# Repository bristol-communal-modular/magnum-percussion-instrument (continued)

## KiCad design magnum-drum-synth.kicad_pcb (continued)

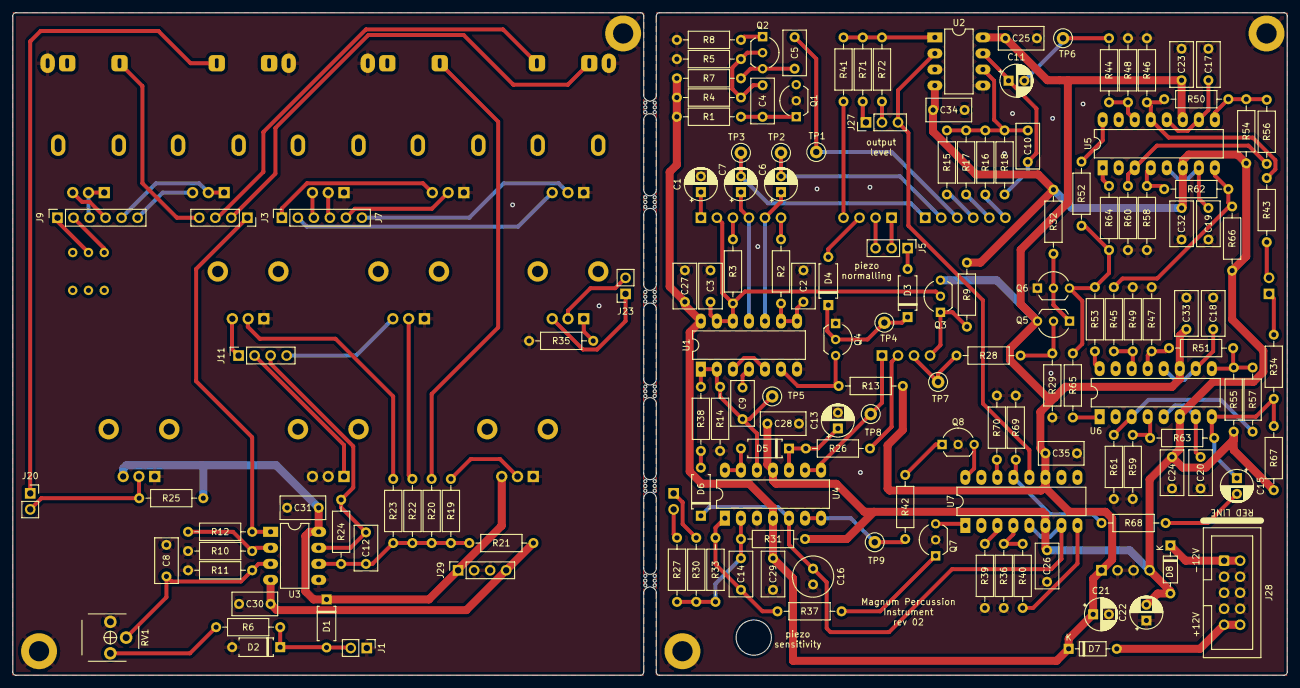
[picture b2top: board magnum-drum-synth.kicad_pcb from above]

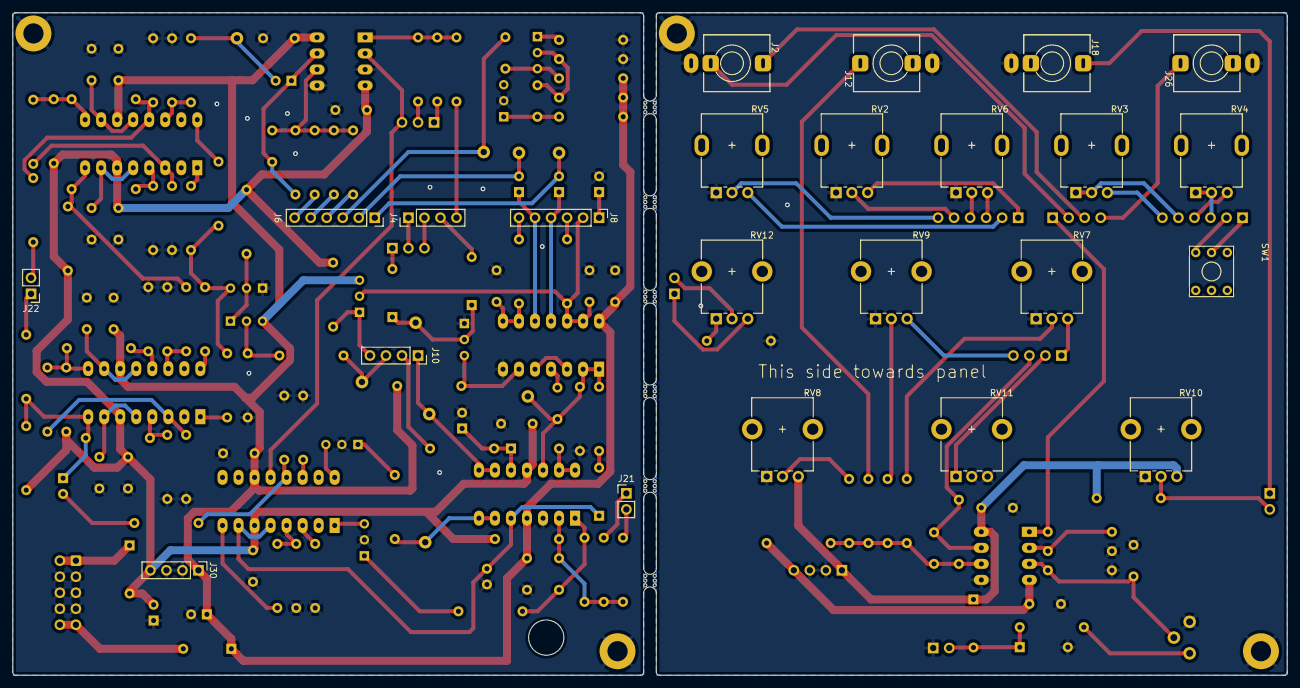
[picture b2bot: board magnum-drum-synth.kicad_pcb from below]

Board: 2 copper layers, 202.0 x 105.0 mm, 184 parts (23 on the bottom side), 121 nets.

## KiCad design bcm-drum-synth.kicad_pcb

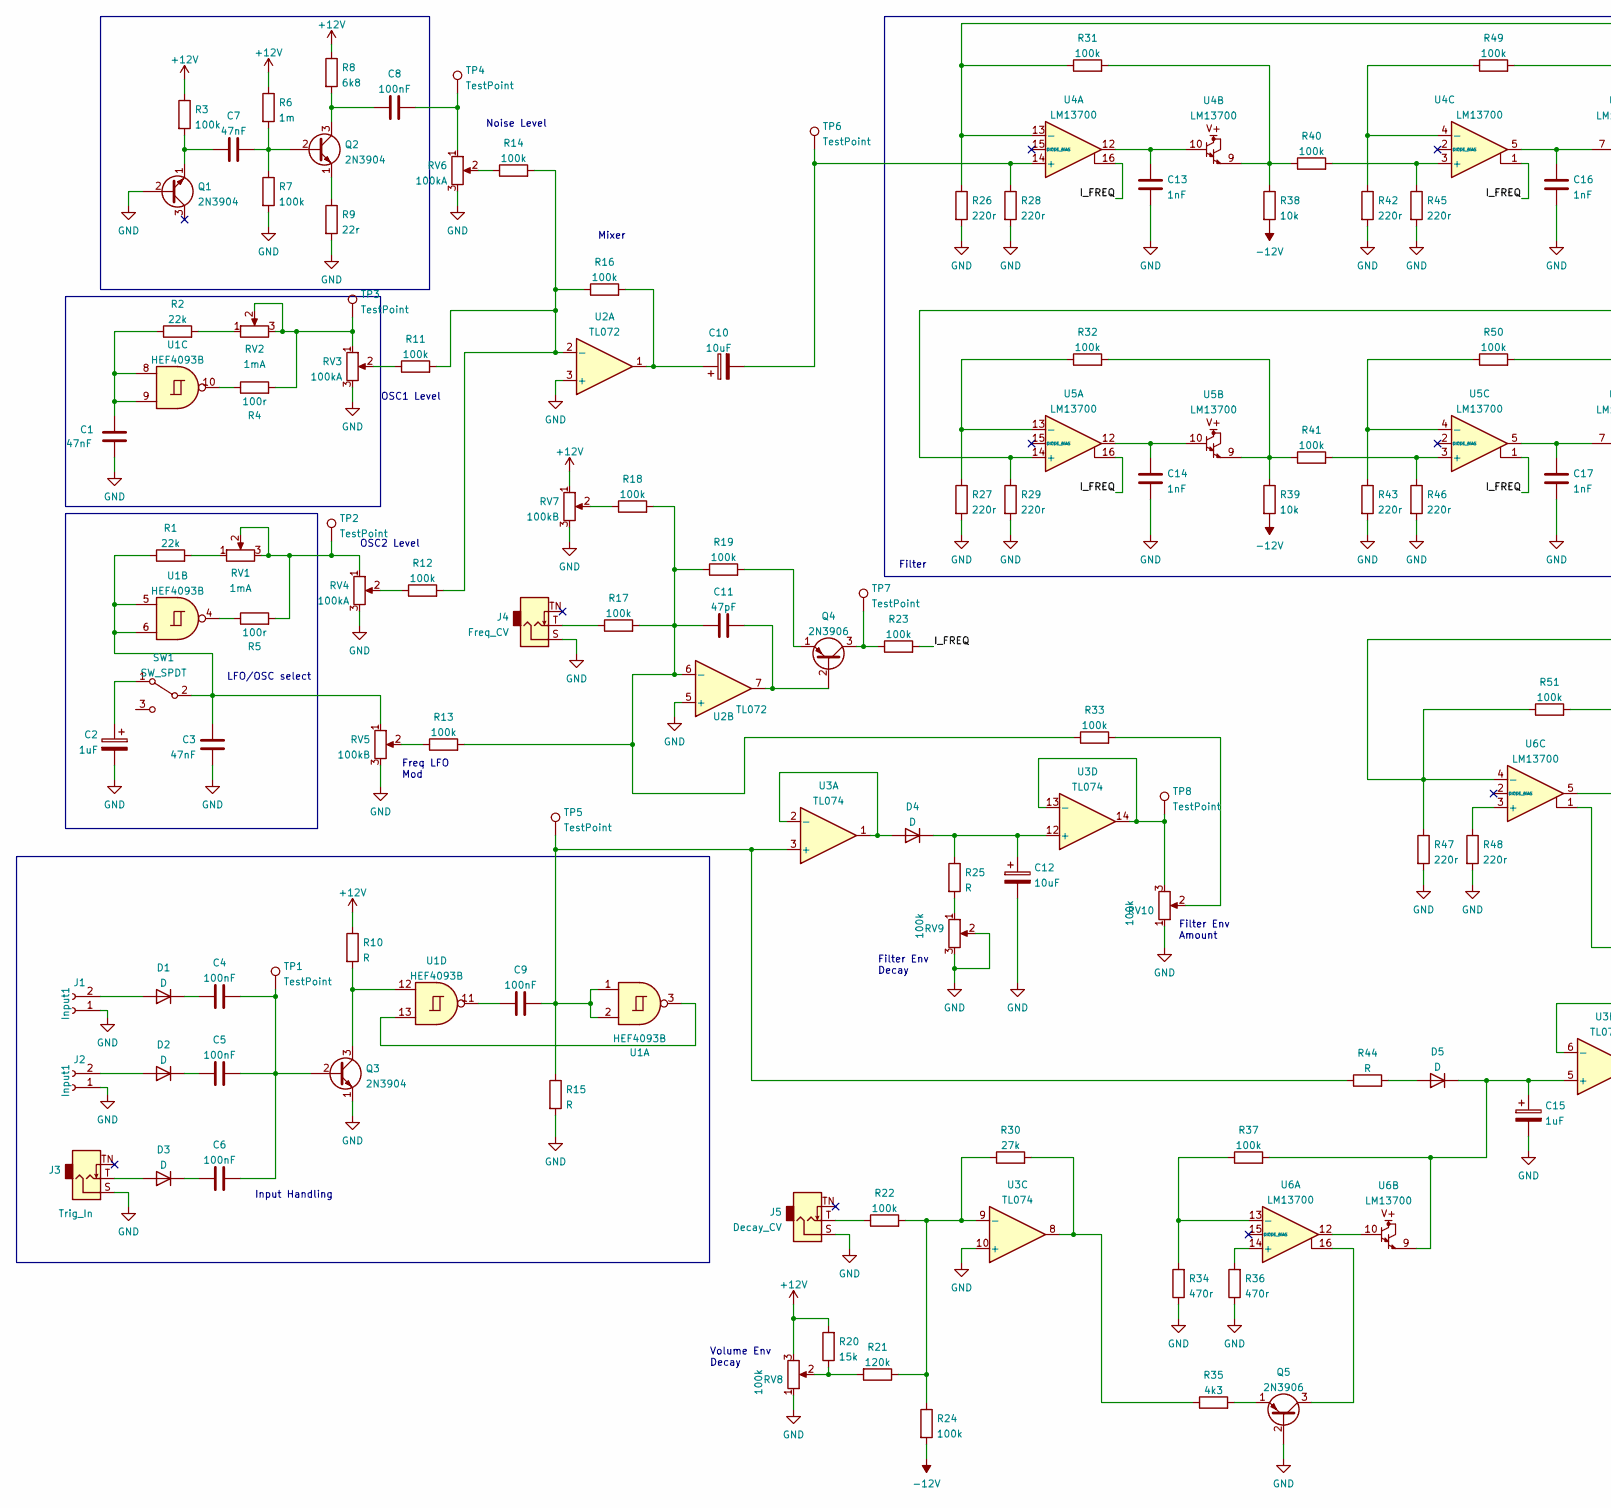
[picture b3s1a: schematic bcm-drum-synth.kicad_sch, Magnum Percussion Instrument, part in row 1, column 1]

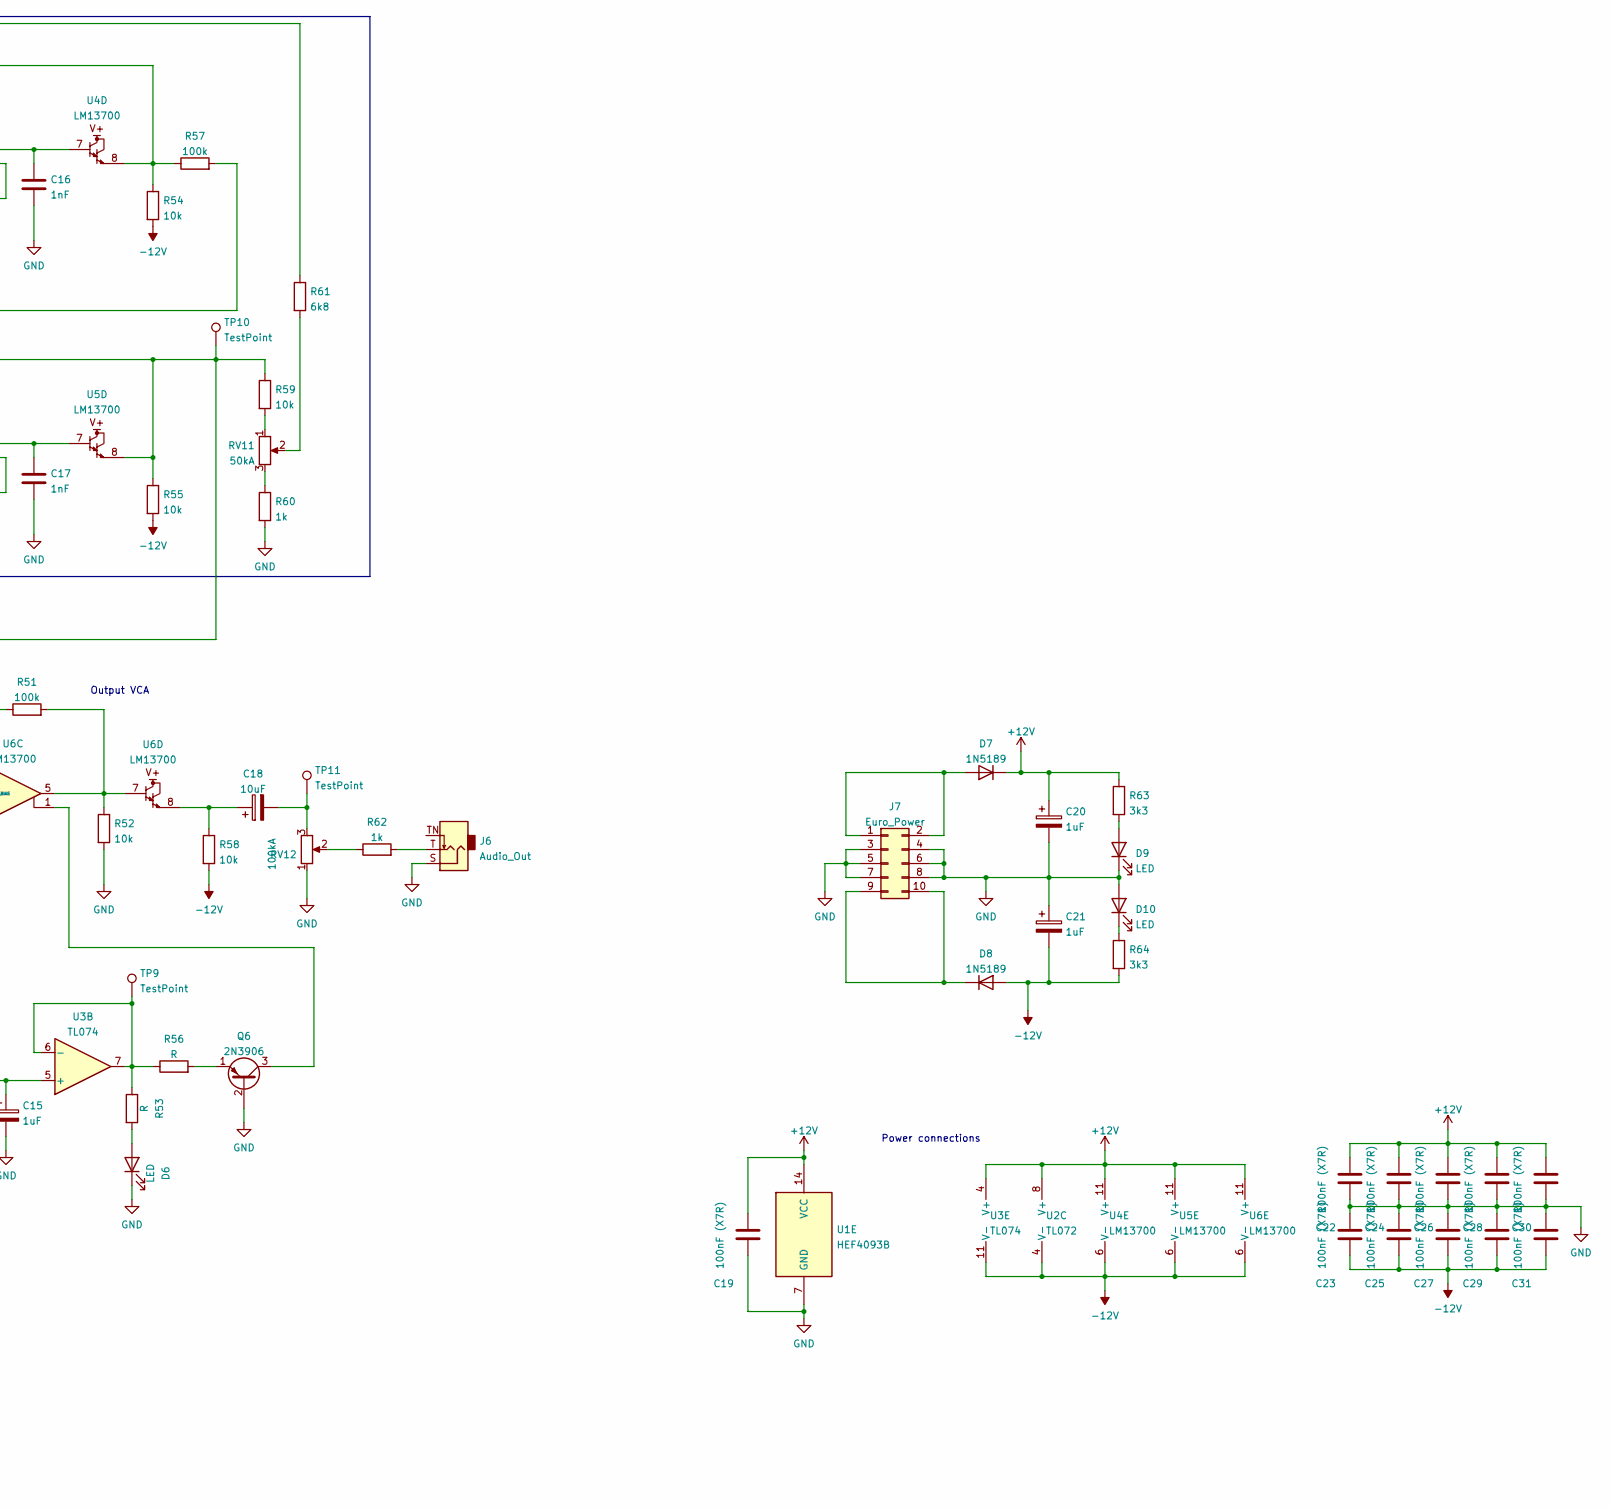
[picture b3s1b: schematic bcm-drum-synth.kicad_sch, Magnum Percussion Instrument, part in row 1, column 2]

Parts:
C1, C3, C7: 47nF; C_Rect_L7.0mm_W3.5mm_P2.50mm_P5.00mm
C2, C15, C20, C21: 1uF; CP_Radial_D5.0mm_P2.50mm
C4, C5, C6, C8, C9: 100nF; C_Rect_L7.0mm_W3.5mm_P2.50mm_P5.00mm
C10, C12, C18: 10uF; CP_Radial_D5.0mm_P2.50mm
C11: 47pF; C_Rect_L7.0mm_W3.5mm_P2.50mm_P5.00mm
C13, C14, C16, C17: 1nF; C_Rect_L7.0mm_W3.5mm_P2.50mm_P5.00mm
C19, C22, C23, C24, C25, C26, C27, C28, C29, C30, C31: 100nF (X7R); C_Rect_L7.0mm_W3.5mm_P2.50mm_P5.00mm
D1, D2, D3, D4, D5: D; Diode_THT_P7.62mm_Horizontal
D6, D9, D10: LED; LED_D5.0mm
D7, D8: 1N5189; D_DO-35_SOD27_P7.62mm_Horizontal
J1, J2: Input1; PinHeader_1x02_P2.54mm_Vertical
J3: Trig_In; Jack_3.5mm_QingPu_WQP-PJ398SM_Vertical
J4: Freq_CV; Jack_3.5mm_QingPu_WQP-PJ398SM_Vertical
J5: Decay_CV; Jack_3.5mm_QingPu_WQP-PJ398SM_Vertical
J6: Audio_Out; Jack_3.5mm_QingPu_WQP-PJ398SM_Vertical
J7: Euro_Power; EurorackPowerHeader_2x05_P2.54mm_Shrouded
Q1, Q2, Q3: 2N3904; TO-92_Inline_Wide
Q4, Q5, Q6: 2N3906; TO-92_Inline_Wide
R1, R2: 22k; R_Axial_DIN0207_L6.3mm_D2.5mm_P7.62mm_Horizontal
R3, R7, R11, R12, R13, R14, R16, R17, R18, R19, R22, R23, R24, R31, R32, R33, R37, R40, R41, R49, R50, R51, R57: 100k; R_Axial_DIN0207_L6.3mm_D2.5mm_P7.62mm_Horizontal
R4, R5: 100r; R_Axial_DIN0207_L6.3mm_D2.5mm_P7.62mm_Horizontal
R6: 1m; R_Axial_DIN0207_L6.3mm_D2.5mm_P7.62mm_Horizontal
R8, R61: 6k8; R_Axial_DIN0207_L6.3mm_D2.5mm_P7.62mm_Horizontal
R9: 22r; R_Axial_DIN0207_L6.3mm_D2.5mm_P7.62mm_Horizontal
R10, R15, R25, R44, R53, R56: R; R_Axial_DIN0207_L6.3mm_D2.5mm_P7.62mm_Horizontal
R20: 15k; R_Axial_DIN0207_L6.3mm_D2.5mm_P7.62mm_Horizontal
R21: 120k; R_Axial_DIN0207_L6.3mm_D2.5mm_P7.62mm_Horizontal
R26, R27, R28, R29, R42, R43, R45, R46, R47, R48: 220r; R_Axial_DIN0207_L6.3mm_D2.5mm_P7.62mm_Horizontal
R30: 27k; R_Axial_DIN0207_L6.3mm_D2.5mm_P7.62mm_Horizontal
R34, R36: 470r; R_Axial_DIN0207_L6.3mm_D2.5mm_P7.62mm_Horizontal
R35: 4k3; R_Axial_DIN0207_L6.3mm_D2.5mm_P7.62mm_Horizontal
R38, R39, R52, R54, R55, R58, R59: 10k; R_Axial_DIN0207_L6.3mm_D2.5mm_P7.62mm_Horizontal
R60, R62: 1k; R_Axial_DIN0207_L6.3mm_D2.5mm_P7.62mm_Horizontal
R63, R64: 3k3; R_Axial_DIN0207_L6.3mm_D2.5mm_P7.62mm_Horizontal
RV1, RV2: 1mA; Potentiometer_Alpha_RD901F-40-00D_Single_Vertical_CircularH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
RV3, RV4, RV6, RV12: 100kA; Potentiometer_Alpha_RD901F-40-00D_Single_Vertical_CircularH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
RV5, RV7: 100kB; Potentiometer_Alpha_RD901F-40-00D_Single_Vertical_CircularH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
RV8, RV9, RV10: 100k; Potentiometer_Alpha_RD901F-40-00D_Single_Vertical_CircularH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
RV11: 50kA; Potentiometer_Alpha_RD901F-40-00D_Single_Vertical_CircularH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
SW1: SW_SPDT; SW_SPDT_DailyWell_MiniToggle
TP1, TP2, TP3, TP4, TP5, TP6, TP7, TP8, TP9, TP10, TP11: TestPoint; TestPoint_Loop_D2.50mm_Drill1.0mm_LowProfile
U1: HEF4093B; DIP-14_W7.62mm_LongPads
U2: TL072; DIP-8_W7.62mm_LongPads
U3: TL074; DIP-14_W7.62mm_LongPads
U4, U5, U6: LM13700; DIP-16_W7.62mm_LongPads

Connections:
+12V: C19.1, C20.1, C22.1, C24.1, C26.1, C28.1, C30.1, D7.1 (K), R3.1, R6.1, R8.1, R10.1, R20.2, R63.1, RV7.1, RV8.3, U1.14 (VCC), U2.8 (V+), U3.4 (V+), U4.11 (V+), U5.11 (V+), U6.11 (V+)
-12V: C21.2, C23.2, C25.2, C27.2, C29.2, C31.2, D8.2 (A), R24.2, R38.2, R39.2, R54.2, R55.2, R58.2, R64.2, U2.4 (V-), U3.11 (V-), U4.6 (V-), U5.6 (V-), U6.6 (V-)
/I_FREQ: R23.2, U4.1, U4.16, U5.1, U5.16
GND: C1.1, C2.2, C3.1, C12.2, C13.1, C14.1, C15.2, C16.1, C17.1, C19.2, C20.2, C21.1, C22.2, C23.1, C24.2, C25.1, C26.2, C27.1, C28.2, C29.1, C30.2, C31.1, D6.1 (K), D9.1 (K), D10.2 (A), J1.1, J2.1, J3.S, J4.S, J5.S, J6.S, J7.3, J7.4, J7.5, J7.6, J7.7, J7.8, Q1.2 (B), Q3.1 (E), Q5.2 (B), Q6.2 (B), R7.2, R9.2, R15.2, R26.2, R27.2, R28.2, R29.2, R34.1, R36.1, R42.2, R43.2, R45.2, R46.2, R47.2, R48.2, R52.2, R60.2, RV3.3, RV4.3, RV5.3, RV6.3, RV7.3, RV8.1, RV9.2, RV9.3, RV10.1, RV12.1, U1.7 (GND), U2.3 (+), U2.5 (+), U3.10 (+)
unnamed: C1.2, R2.1, U1.8, U1.9
unnamed: C2.1, SW1.1 (A)
unnamed: C3.2, R1.1, RV5.1, SW1.2 (B), U1.5, U1.6
unnamed: C4.1, D1.1 (K)
unnamed: C4.2, C5.2, C6.2, Q3.2 (B), TP1.1
unnamed: C5.1, D2.1 (K)
unnamed: C6.1, D3.1 (K)
unnamed: C7.1, Q1.1 (E), R3.2
unnamed: C7.2, Q2.2 (B), R6.2, R7.1
unnamed: C8.1, Q2.3 (C), R8.2
unnamed: C8.2, RV6.1, TP4.1
unnamed: C9.1, U1.11
unnamed: C9.2, R15.1, R44.1, TP5.1, U1.1, U1.2, U3.3 (+)
unnamed: C10.1, R16.2, U2.1
unnamed: C10.2, R28.1, TP6.1, U4.14 (+)
unnamed: C11.1, R13.2, R17.2, R18.2, R19.1, R33.1, U2.6 (-)
unnamed: C11.2, Q4.2 (B), U2.7
unnamed: C12.1, D4.1 (K), R25.1, U3.12 (+)
unnamed: C13.2, U4.10, U4.12
unnamed: C14.2, U5.10, U5.12
unnamed: C15.1, D5.1 (K), R37.2, U3.5 (+), U6.9
unnamed: C16.2, U4.5, U4.7
unnamed: C17.2, U5.5, U5.7
unnamed: C18.1, R58.1, U6.8
unnamed: C18.2, RV12.3, TP11.1
unnamed: D1.2 (A), J1.2
unnamed: D2.2 (A), J2.2
unnamed: D3.2 (A), J3.T
unnamed: D4.2 (A), U3.1, U3.2 (-)
unnamed: D5.2 (A), R44.2
unnamed: D6.2 (A), R53.2
unnamed: D7.2 (A), J7.1, J7.2
unnamed: D8.1 (K), J7.9, J7.10
unnamed: D9.2 (A), R63.2
unnamed: D10.1 (K), R64.1
unnamed: J4.T, R17.1
unnamed: J5.T, R22.1
unnamed: J6.T, R62.2
unnamed: Q2.1 (E), R9.1
unnamed: Q3.3 (C), R10.2, U1.12
unnamed: Q4.1 (E), R19.2
unnamed: Q4.3 (C), R23.1, TP7.1
unnamed: Q5.1 (E), R35.2
unnamed: Q5.3 (C), U6.16
unnamed: Q6.1 (E), R56.2
unnamed: Q6.3 (C), U6.1
unnamed: R1.2, RV1.1
unnamed: R2.2, RV2.1
unnamed: R4.1, U1.10
unnamed: R4.2, RV2.2, RV2.3, RV3.1, TP3.1
unnamed: R5.1, U1.4
unnamed: R5.2, RV1.2, RV1.3, RV4.1, TP2.1
unnamed: R11.1, RV3.2
unnamed: R11.2, R12.2, R14.2, R16.1, U2.2 (-)
unnamed: R12.1, RV4.2
unnamed: R13.1, RV5.2
unnamed: R14.1, RV6.2
unnamed: R18.1, RV7.2
unnamed: R20.1, R21.2, RV8.2
unnamed: R21.1, R22.2, R24.1, R30.1, U3.9 (-)
unnamed: R25.2, RV9.1
unnamed: R26.1, R31.1, R61.1, U4.13 (-)
unnamed: R27.1, R32.1, U5.13 (-)
unnamed: R29.1, R57.2, U5.14 (+)
unnamed: R30.2, R35.1, U3.8
unnamed: R31.2, R38.1, R40.1, U4.9
unnamed: R32.2, R39.1, R41.1, U5.9
unnamed: R33.2, RV10.2
unnamed: R34.2, R37.1, U6.13 (-)
unnamed: R36.2, U6.14 (+)
unnamed: R40.2, R45.1, U4.3 (+)
unnamed: R41.2, R46.1, U5.3 (+)
unnamed: R42.1, R49.1, U4.4 (-)
unnamed: R43.1, R50.1, U5.4 (-)
unnamed: R47.1, R50.2, R51.1, R55.1, R59.1, TP10.1, U5.8, U6.4 (-)
unnamed: R48.1, U6.3 (+)
unnamed: R49.2, R54.1, R57.1, U4.8
unnamed: R51.2, R52.1, U6.5, U6.7
unnamed: R53.1, R56.1, TP9.1, U3.6 (-), U3.7
unnamed: R59.2, RV11.1
unnamed: R60.1, RV11.3
unnamed: R61.2, RV11.2
unnamed: R62.1, RV12.2
unnamed: RV10.3, TP8.1, U3.13 (-), U3.14
unnamed: U1.3, U1.13
unnamed: U6.10, U6.12

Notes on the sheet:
OSC2 Level
Noise Level
Input Handling
Filter
Mixer
Volume Env Decay
Filter Env Decay
LFO/OSC select
Output VCA
Freq LFO Mod
OSC1 Level
Filter Env Amount
Power connections

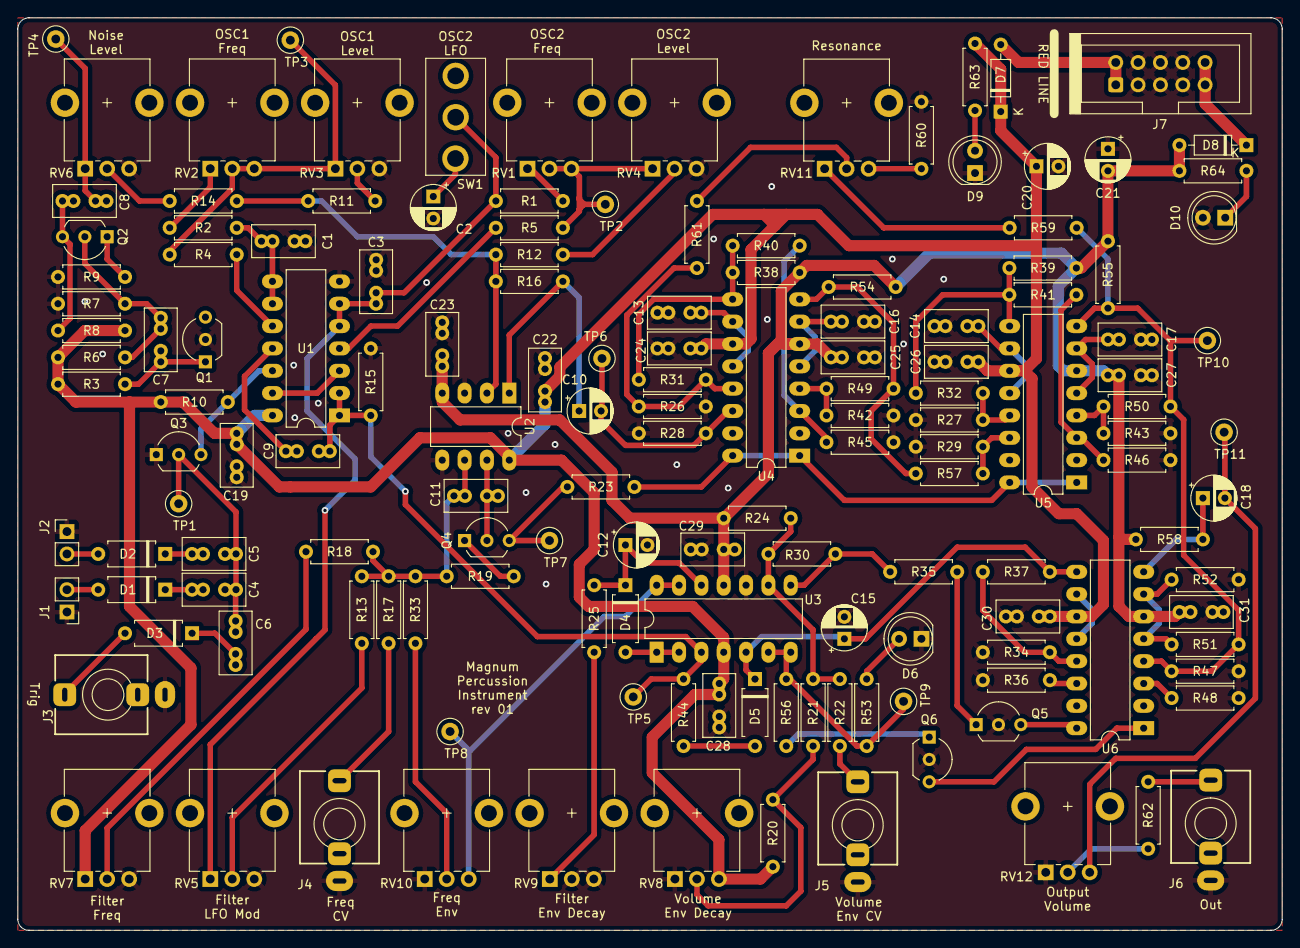
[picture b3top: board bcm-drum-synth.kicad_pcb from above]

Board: 2 copper layers, 143.8 x 103.8 mm, 148 parts (0 on the bottom side), 90 nets.

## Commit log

2022-04-04 Adding readme
2022-04-04 Updating schematic some more
2022-04-04 Adding some info to schematic
2022-04-11 Rev 1
2022-04-11 Changing name of project
2022-04-11 Update schematic
2022-05-14 Creating rev02
2022-06-18 Updating after tweaks and project improvements
2022-06-26 Update BOM generation config
2022-06-26 Further tweaks and layout improvements
2022-06-29 Finalising rev3
2022-06-29 organising folders
2022-07-19 Tweaking schematic and bom values
2022-07-19 Adding basic build guide
2022-07-19 Adding partnumbers csv
2022-07-19 Mentioning the build folder in the readme
2022-08-31 Update front panel with new design
2022-08-31 Adding inkscape svg file for pcb panel layers
2022-09-23 Adding files for next revision of front panel
2022-10-16 Final tweaks to rev 4
2022-10-16 replotting rev4 gerbers
2022-10-16 Final export of everything for rev4
2022-10-17 Updating partnumbers and build info
2022-12-07 Adding License
    CC BY-NC-SA 4.0
2022-12-07 Adding files for manual and related bits
2022-12-11 Adding parts guide
2022-12-11 Adding partslist csv
2022-12-14 Initial site
2022-12-23 Updating website
2022-12-23 Moving mixer opamp to front board
2022-12-23 Rejigging interconnects
2022-12-23 Fixing trigger piezo normalling
2022-12-23 Tweaking silkscreen
2022-12-23 Move decay env CV summing to front board
2022-12-24 slimlining opamp count and more moving around
2023-05-08 Final fixes and tweaks (hopefully)
2023-05-08 Updating layout text for better soldering guide
2023-05-08 geographically reannotate all the parts
2023-05-09 Fixing power header in wrong place
2023-05-09 Final tweaks to PCB
2023-05-09 Generating gerbers for rev5
2023-05-09 Updating parts guide and adding svg version
2023-05-09 remember to update schematic rev to r05
2023-05-09 recreating schematic
2023-05-09 Update boms and partslists
2023-05-09 Update build docs
2023-05-20 Update kicad project for v7
2023-07-11 Final board tweaks
2023-07-15 Generating new gerbers
2023-07-19 rev06 gerbers
2024-01-11 Final tweaks
2024-01-11 replotting gerbers
2024-01-11 Adding panel affinity design file
